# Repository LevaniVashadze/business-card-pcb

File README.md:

# business-card-pcb
My first ever time designing a PCB, based on parts from https://solder.hackclub.com

It has a button, which activates 2 led lights and a small vibrating motor.

Silk screened is my website and the qr form of my website link.

# BOM:

- 3 resistors
- 2 LED lights
- 1 transistor
- 1 button
- 1 battery cell
- 1 mini motor disc
- 1 capacitor

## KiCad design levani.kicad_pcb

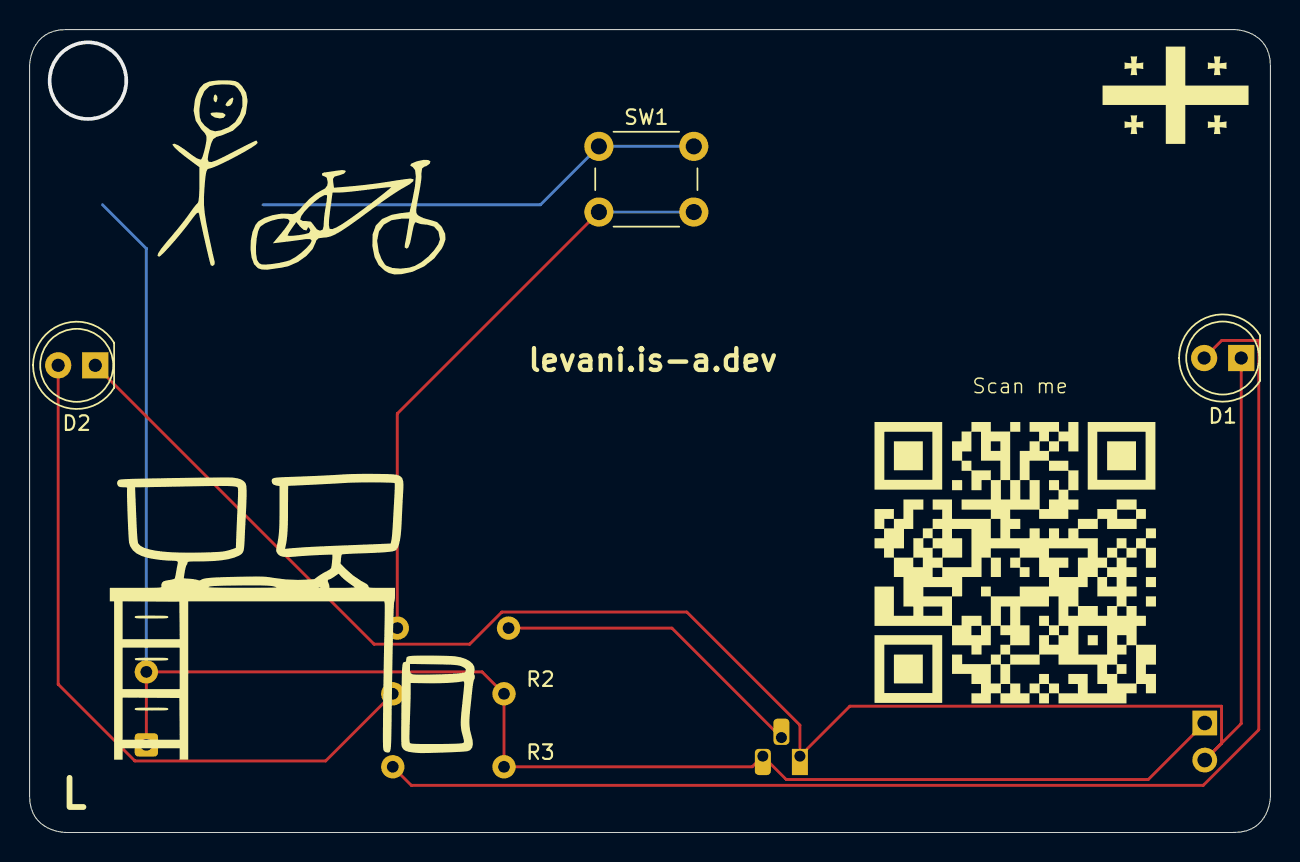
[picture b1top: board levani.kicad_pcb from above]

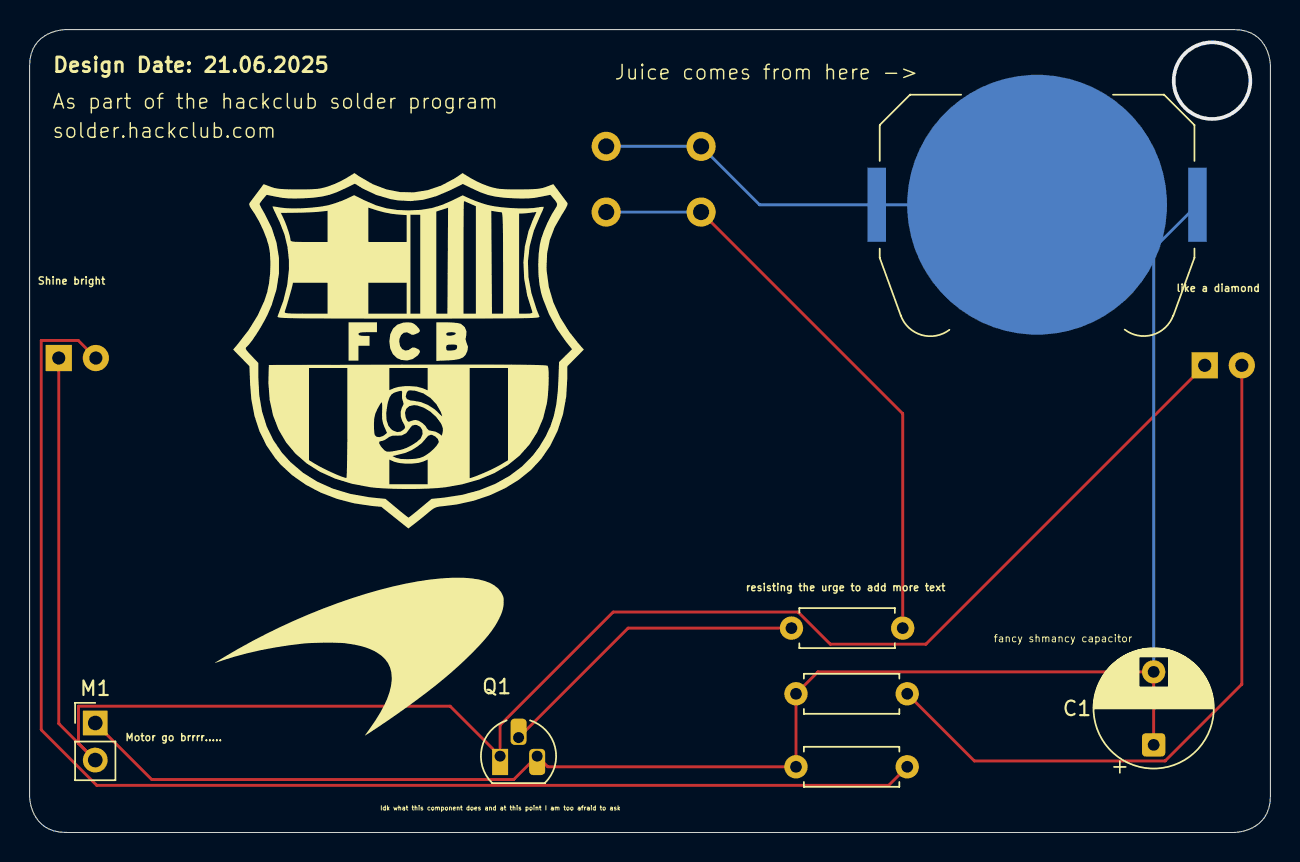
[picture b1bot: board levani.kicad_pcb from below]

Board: 2 copper layers, 85.0 x 55.0 mm, 10 parts (7 on the bottom side), 6 nets.

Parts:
BT1: Battery_Cell; BatteryHolder_Keystone_3034_1x20mm
C1: C; CP_Radial_D8.0mm_P5.00mm
D1, D2: LED; LED_D5.0mm
M1: Motor_DC; PinHeader_1x02_P2.54mm_Vertical
Q1: NPN; TO-92L_HandSolder
R1, R2, R3: R; R_Axial_DIN0207_L6.3mm_D2.5mm_P7.62mm_Horizontal
SW1: SW_Push; SW_PUSH_6mm

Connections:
unnamed: BT1.1 (+), BT1.2 (-), C1.1, C1.2, M1.1 (+), Q1.3 (E), R2.1, R3.1, SW1.1
unnamed: D1.2 (A), R3.2
unnamed: D1.1 (K), D2.1 (K), M1.2 (-), Q1.1 (C)
unnamed: D2.2 (A), R2.2
unnamed: Q1.2 (B), R1.2
unnamed: R1.1, SW1.2

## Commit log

2025-06-20 init
2025-06-21 fix schematic and add more silkscreened text
2025-06-21 update schematic with more art
2025-07-01 add drill files
